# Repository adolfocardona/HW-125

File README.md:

# HW-125

KiCad Sd Card Schematic

Download Seeed OPL https://github.com/Seeed-Studio/OPL_Kicad_Library

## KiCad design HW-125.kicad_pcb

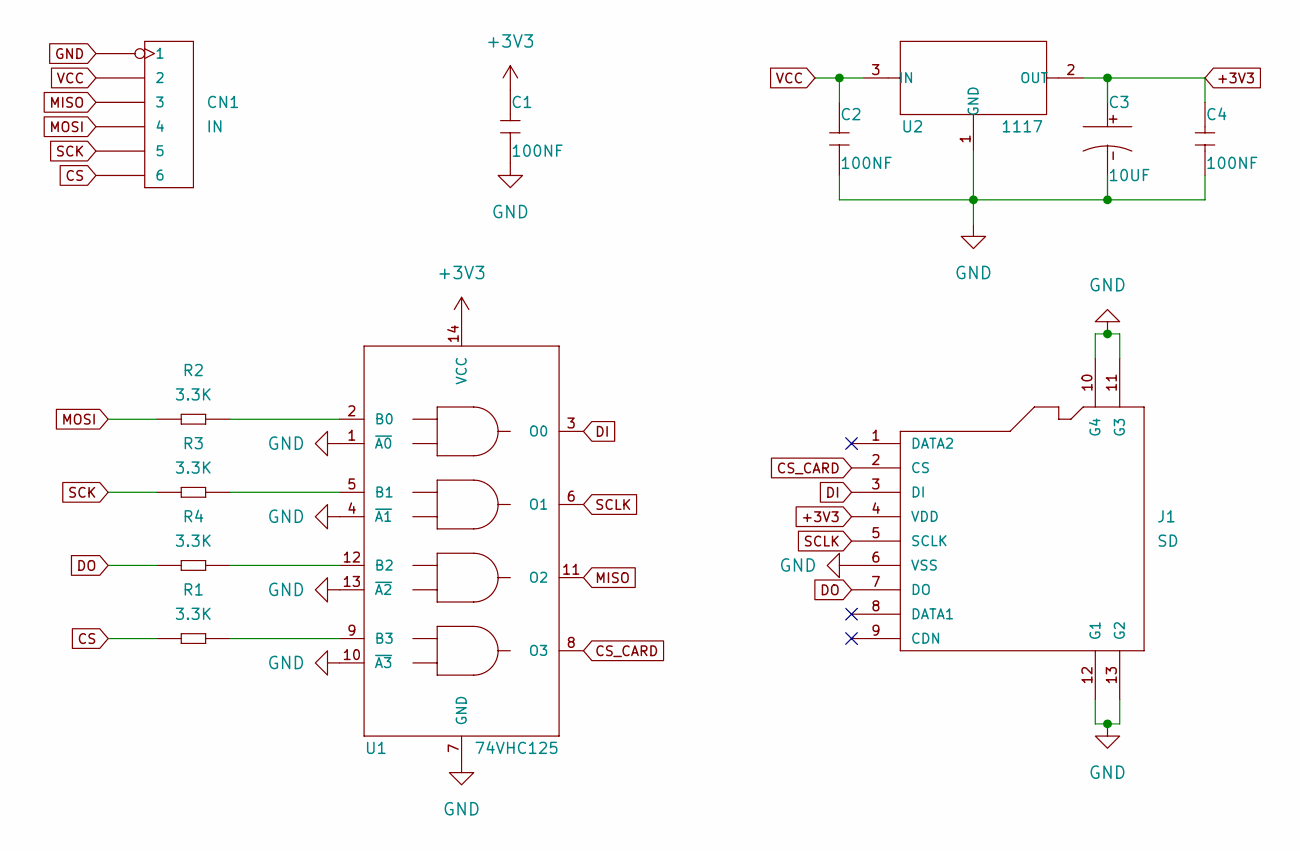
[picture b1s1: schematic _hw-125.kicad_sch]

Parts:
C1, C2, C4: 100NF; C0603; MPN CC0603KRX7R9BB104
C3: 10UF; AVX-A(1206); MPN TAJA106K010RNJ
CN1: IN; H6-2.54; MPN F185-1106A1BSYC1
J1: SD; MICRO-SD9+4P-SMD-16.1X14.5X1.85MM
R1, R2, R3, R4: 3.3K; R0603; MPN RC0603FR-073K3L
U1: 74VHC125; TSSOP14-0.65-5X4.4MM; MPN 74VHC125MTCX
U2: 1117; SOT-223; MPN CJT1117-3.3

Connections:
+3V3: C1.2, C3.1 (+), C4.2, J1.4 (VDD), U1.14 (VCC), U2.2 (OUT), U2.TER (OUT)
CS: CN1.6, R1.1
CS_CARD: J1.2 (CS), U1.8 (O3)
DI: J1.3 (DI), U1.3 (O0)
DO: J1.7 (DO), R4.1
GND: C1.1, C2.1, C3.2 (-), C4.1, CN1.1, J1.6 (VSS), J1.10 (G4), J1.11 (G3), J1.12 (G1), J1.13 (G2), U1.1 (~A0), U1.4 (~A1), U1.7 (GND), U1.10 (~A3), U1.13 (~A2), U2.1 (GND)
MISO: CN1.3, U1.11 (O2)
MOSI: CN1.4, R2.1
unnamed: R1.2, U1.9 (B3)
unnamed: R2.2, U1.2 (B0)
unnamed: R3.2, U1.5 (B1)
unnamed: R4.2, U1.12 (B2)
SCK: CN1.5, R3.1
SCLK: J1.5 (SCLK), U1.6 (O1)
VCC: C2.2, CN1.2, U2.3 (IN)

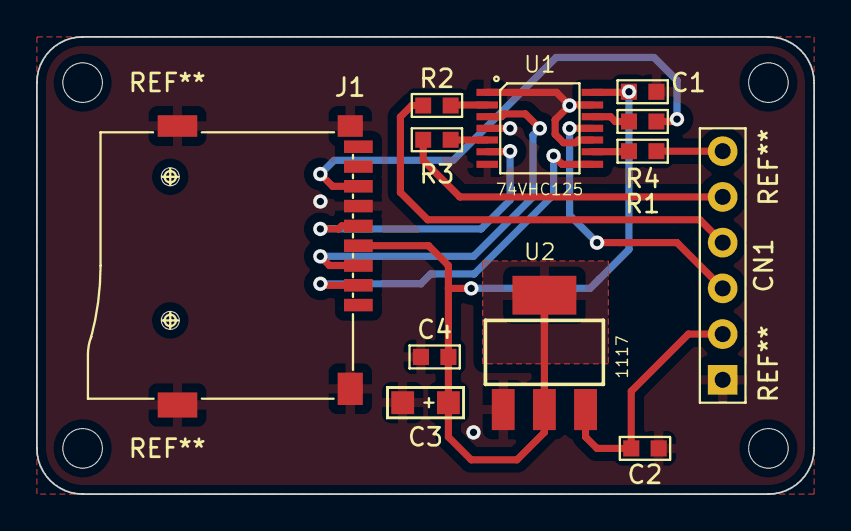
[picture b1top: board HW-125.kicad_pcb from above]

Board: 2 copper layers, 43.2 x 25.4 mm, 12 parts (0 on the bottom side), 15 nets.
